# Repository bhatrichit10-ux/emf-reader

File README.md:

# Richit's EMF Reader

This is a basic project which is an EMF Reader like the one in Phasmophobia game!

# Images
## Schematics
Magnometer: <br>
 <br>
Neopixels : <br>
 <br>
Microcontroller: <br>
 <br>

## PCB
2D View: <br>
 <br>

3D View: <br>

## CAD

# BOM

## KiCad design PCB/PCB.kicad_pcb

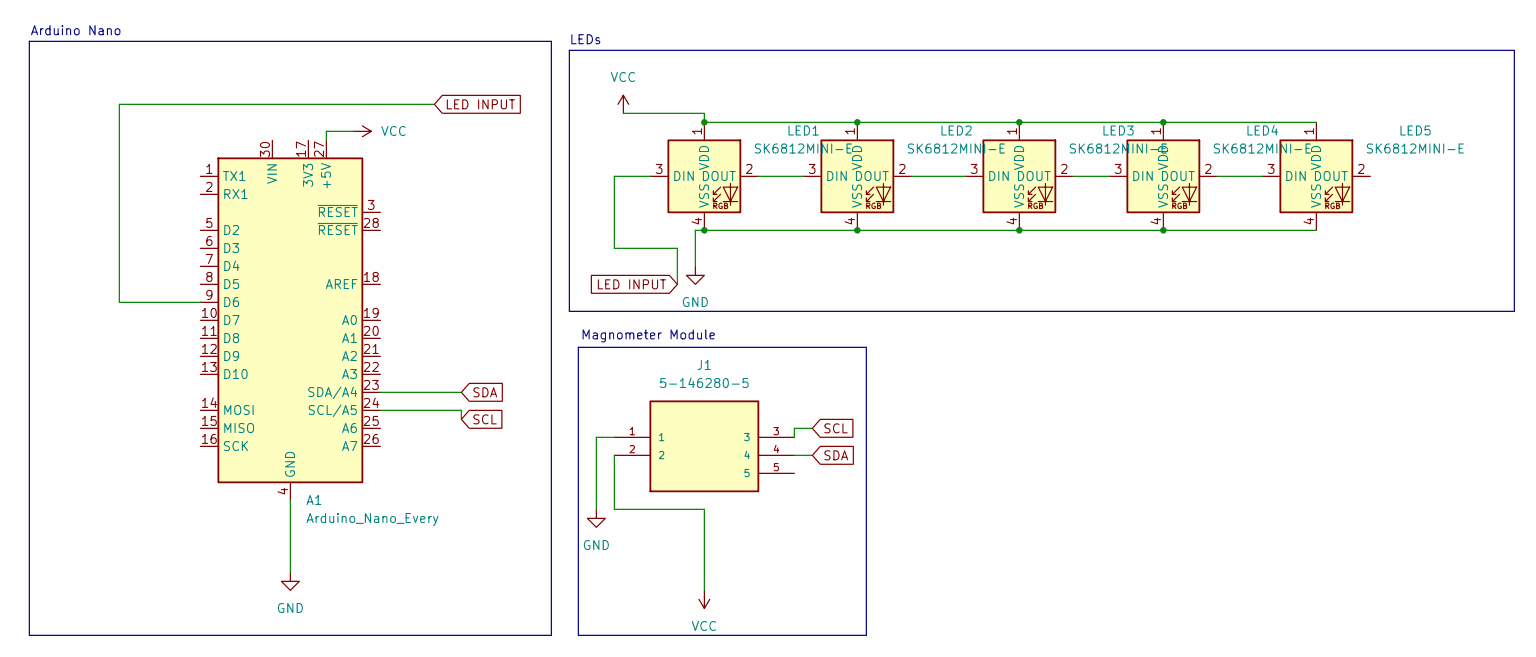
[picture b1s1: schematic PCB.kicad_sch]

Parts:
A1: Arduino_Nano_Every; Arduino_Nano
J1: 5-146280-5; TE_5-146280-5; PARTREV R
LED1, LED2, LED3, LED4, LED5: SK6812MINI-E; LED_6028R

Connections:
GND: A1.4 (GND), A1.29 (GND), J1.1, LED1.4 (VSS), LED2.4 (VSS), LED3.4 (VSS), LED4.4 (VSS), LED5.4 (VSS)
LED INPUT: A1.9 (D6), LED1.3 (DIN)
unnamed: LED1.2 (DOUT), LED2.3 (DIN)
unnamed: LED2.2 (DOUT), LED3.3 (DIN)
unnamed: LED3.2 (DOUT), LED4.3 (DIN)
unnamed: LED4.2 (DOUT), LED5.3 (DIN)
SCL: A1.24 (SCL/A5), J1.3
SDA: A1.23 (SDA/A4), J1.4
VCC: A1.27 (+5V), J1.2, LED1.1 (VDD), LED2.1 (VDD), LED3.1 (VDD), LED4.1 (VDD), LED5.1 (VDD)

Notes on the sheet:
LEDs
Magnometer Module
Arduino Nano

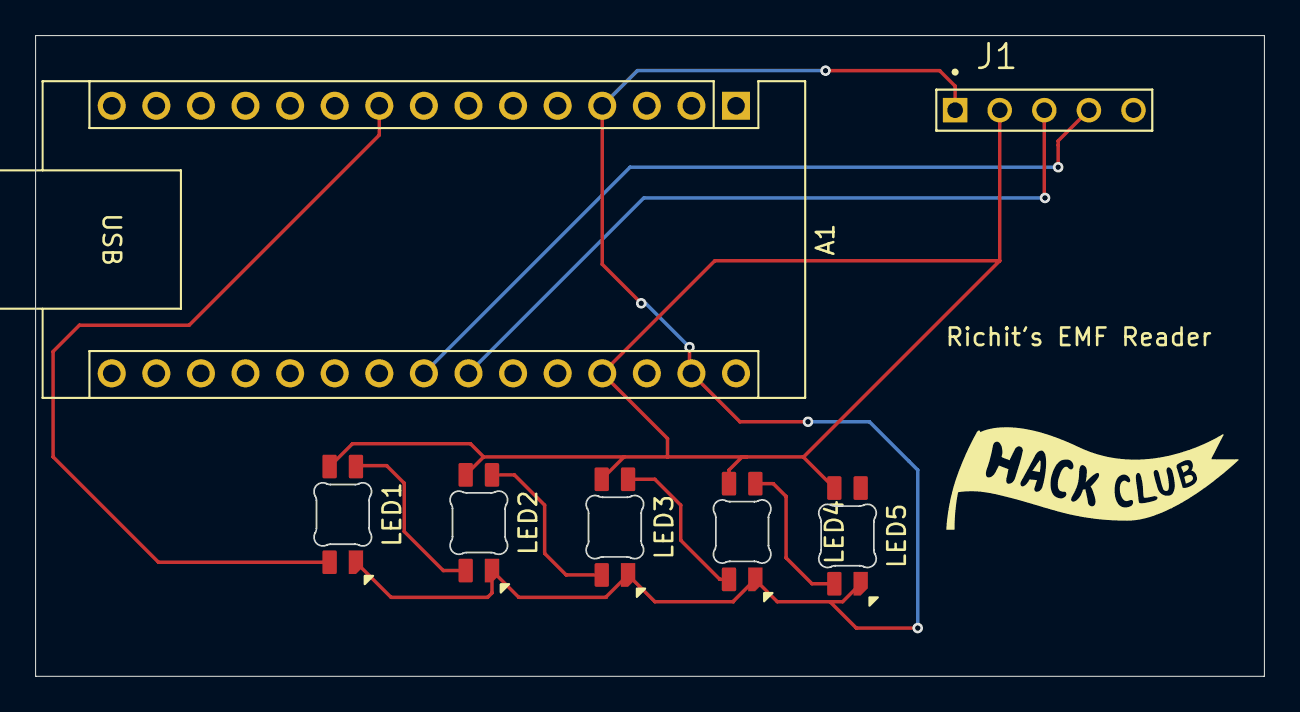
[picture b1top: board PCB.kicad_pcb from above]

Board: 2 copper layers, 70.0 x 36.5 mm, 7 parts (0 on the bottom side), 9 nets.

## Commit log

2026-03-04 PCB DESIGNED!
2026-03-04 Exported Gerber and other stuff too
2026-03-04 firmware done
2026-03-04 some stuff
2026-03-04 Ready to SHIP!
